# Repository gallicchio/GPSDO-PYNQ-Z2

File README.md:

# GPSDO-PYNQ-Z2

**Compare up to 13 GPS Disciplined Oscillators: 10 MHz and 1PPS**

A board for a [PYNQ-Z2](http://www.pynq.io/boards.html) that measures the phase of thirteen 10 MHz references
against each other in 12 ps steps, with a floor below a picosecond. Rev A is built and measured. **Rev B is in
hand, and has not been tested yet.**

Rev A after its bench life: the red wire and the blue resistors are the repairs.

<table>
<tr>
<td width="50%"></td>
<td width="50%"></td>
</tr>
<tr><td colspan="2">Rev A on its PYNQ-Z2, being measured against generators and a scope, October 2026.</td></tr>
</table>

Rev B, as drawn in KiCad:

<p>  </p>

Click any image to open it at full size.

## At a glance

| | |
|---|---|
| Inputs | 13 x 10 MHz and 12 x 1 pps, on SMA |
| Method | digital dual-mixer time difference (DDMTD), one helper clock for every channel |
| Step | 12.34 ps a count |
| Floor, rev A | Allan deviation 2.8e-12 at 1 s, 2.8e-15 at 1000 s; time deviation 0.18 ps at 1 s |
| 1 pps | a 10 ns counter across all twelve |
| Host | PYNQ-Z2 (Zynq-7020), on its Raspberry Pi header; a Python driver |
| Board | 207 x 180 mm, 4 layers, 27 SMA jacks, 5 V from the PYNQ |
| Cost | about $246 for two assembled (rev B's estimate, bare boards extra) |
| Status | rev A: built, repaired by hand, measured. Rev B: in hand, untested |

The files in this repository are rev B. Rev A is the tag `GPSDO-PYNQ-Z2-revA` and
[`GPSDO-PYNQ-Z2-revA.zip`](GPSDO-PYNQ-Z2-revA.zip).

## How it works

- **A helper clock 1234.4 Hz away from 10 MHz** samples every input in a flip-flop.
- **Each input comes out as a 1234.4 Hz beat** with the same phase, stretched 8101 times in time.
- **A plain counter in the FPGA** times the beat edges. No carry chains, no calibration: one count is 12.34 ps.
- **The helper is common to every channel**, so its own noise cancels when two channels are compared.
- **Only slow beats cross to the FPGA.** The 10 MHz never leaves the board.

## What rev A measured

One oven oscillator split to several inputs, so the inputs agree and what is left is the board.

| | measured |
|---|---|
| One beat edge, two inputs from one source | 5.4 ps rms: the counter's own step |
| Allan deviation | 2.8e-12 at 1 s, 2.8e-13 at 10 s, 2.8e-15 at 1000 s (50 Hz bandwidth) |
| Time deviation | 0.18 ps at 1 s, 0.06 ps at 10 s, 0.19 ps at 1000 s |
| Against two GPSDOs' own difference | the floor is 25 times below it at 1 s, 800 times at 10 s |

- These are for channels on the same helper buffer. Rev A has five buffers, and across them it is 12 times
  worse at 1 s. Rev B has one tree.
- **No GPSDO has been through this board yet.** The GPSDO curves were taken on another instrument.
- How it was measured: [`analysis/floor_compare/`](analysis/floor_compare/README.md).

## What rev A got wrong

| fault | on rev A | in rev B |
|---|---|---|
| The synthesizer slipped cycles while reporting lock | cured by a lower output drive, in software | a synthesizer with a proper clock input |
| Inputs with nothing plugged in oscillate | resistors added by hand | a parking jumper on every input |
| The analog 3.3 V had no plane | a strap wire | a plane |
| The 10 MHz monitor output leaks into the channels | kept at low drive | isolated |
| Five helper buffers: channels differ by group | measure within a group | one fan-out tree |

All of it, with the measurements: [`REVB_CHANGES.md`](REVB_CHANGES.md).

## Made with an AI

This was Jason's first board designed with an AI.

- **Nothing is drawn by hand.** About 18,000 lines of Python and Verilog generate the nineteen schematic
  sheets, place every part, route every track, and write the release, the handbook and the gateware.
- **The whole conversation is kept**: 46 rounds of prompts and answers, mistakes included, in
  [`docs/DESIGN_LOG.md`](docs/DESIGN_LOG.md).
- **Three other models reviewed it** before the order: [`design_review/`](design_review/README.md).

What it took to get a working board:

| what went wrong | how it was found |
|---|---|
| A release with no ground planes and no mounting holes passed every check | looking at a render |
| "0 violations" hid 598 errors | making the design-rule check ask more |
| Part rotations for assembly were wrong for six rounds | JLCPCB's own placement preview, the only authority |
| The synthesizer slipped while "locked" | the first real signals on the bench |

| | dates | days |
|---|---|---|
| Rev A design, to the order at JLCPCB | 2026-09-08 to 2026-09-15 | 8 |
| Rev A bring-up and measurement | 2026-09-30 to 2026-10-10 | 11 |
| Rev B design | 2026-10-09 to 2026-10-10 | 2 |
| Rev B ordered | 2026-10-22 | |

Jason Gallicchio, with Claude (Anthropic's Opus 5, Fable 5.1 and Opus 5.5, in Claude Code).

## What is here

| path | what |
|---|---|
| `*.kicad_sch`, `GPSDO-PYNQ-Z2.kicad_pcb` | the KiCad project, rev B |
| [`HANDBOOK.md`](HANDBOOK.md) | every connector, jumper and test point, and how to bring a board up |
| [`mfg/release/`](mfg/release/) | what was uploaded to JLCPCB: Gerbers, BOM, placement |
| [`gateware/`](gateware/README.md) | the Verilog, the Vivado build, the Python driver, the bench programs |
| `gen/`, `pcb/`, `mfg/` | the scripts that generate the design (`python3 build.py`) |
| [`analysis/`](analysis/floor_compare/README.md) | the floor, and how it compares |
| [`docs/DESIGN_LOG.md`](docs/DESIGN_LOG.md) | the design log: every prompt and answer |
| [`photos/`](photos/README.md) | rev A on the bench |

The board grew up in a private repository of the research group. Its commits are here; vendor datasheets are
not. Commit hashes quoted in the documents are the old ones: [`docs/COMMIT_MAP.tsv`](docs/COMMIT_MAP.tsv).

## Licence

Hardware under CERN-OHL-P-2.0, software under MIT: [`LICENSE`](LICENSE).

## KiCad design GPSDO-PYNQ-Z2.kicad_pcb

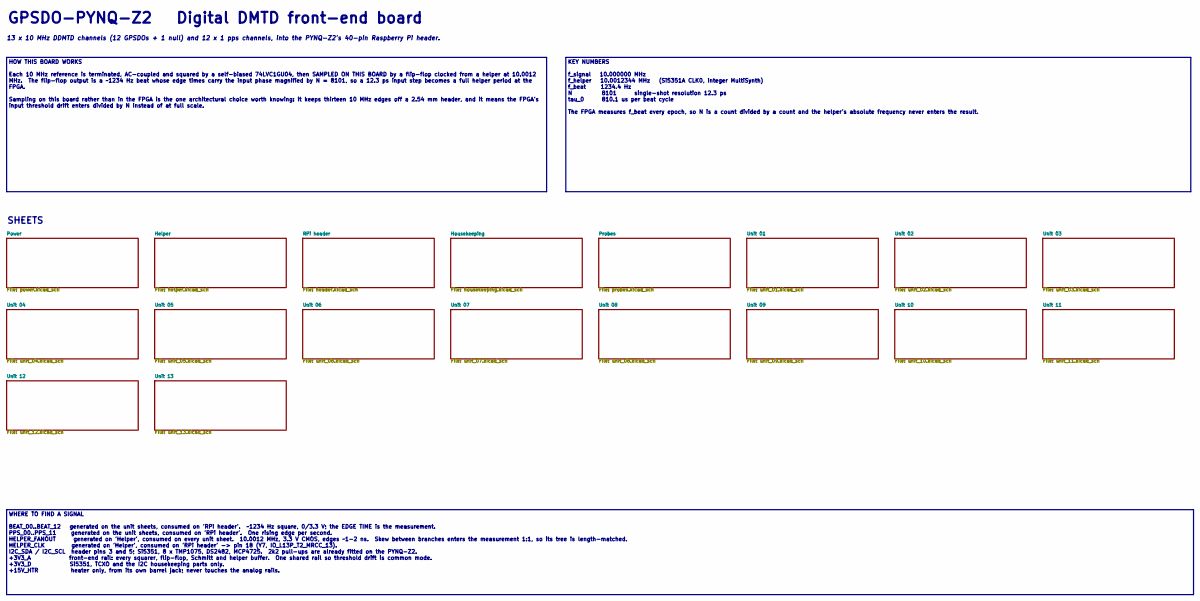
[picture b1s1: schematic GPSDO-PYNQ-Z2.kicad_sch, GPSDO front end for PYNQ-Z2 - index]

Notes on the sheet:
13 x 10 MHz DDMTD channels (12 GPSDOs + 1 null) and 12 x 1 pps channels, into the PYNQ-Z2's 40-pin Raspberry Pi header.
GPSDO-PYNQ-Z2 Digital DMTD front-end board
SHEETS
HOW THIS BOARD WORKS Each 10 MHz reference is terminated, AC-coupled and squared by a self-biased 74LVC1GU04, then SAMPLED ON THIS BOARD by a flip-flop clocked from a helper at 10.0012 MHz. The flip-flop output is a ~1234 Hz beat whose edge times carry the input phase magnified by N = 8101, so a 12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
KEY NUMBERS f_signal 10.000000 MHz f_helper 10.0012344 MHz (Si5351A CLK0, integer MultiSynth) f_beat 1234.4 Hz N 8101 single-shot resolution 12.3 ps tau_0 810.1 us per beat cycle The FPGA measures f_beat every epoch, so N is a count divided by a count and the helper's absolute frequency never enter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
WHERE TO FIND A SIGNAL BEAT_00..BEAT_12 generated on the unit sheets, consumed on 'RPi header'. ~1234 Hz square, 0/3.3 V; the EDGE TIME is the measurement. PPS_00..PPS_11 generated on the unit sheets, consumed on 'RPi header'. One rising edge per second. HELPER_FANOUT generated on 'Helper', consume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

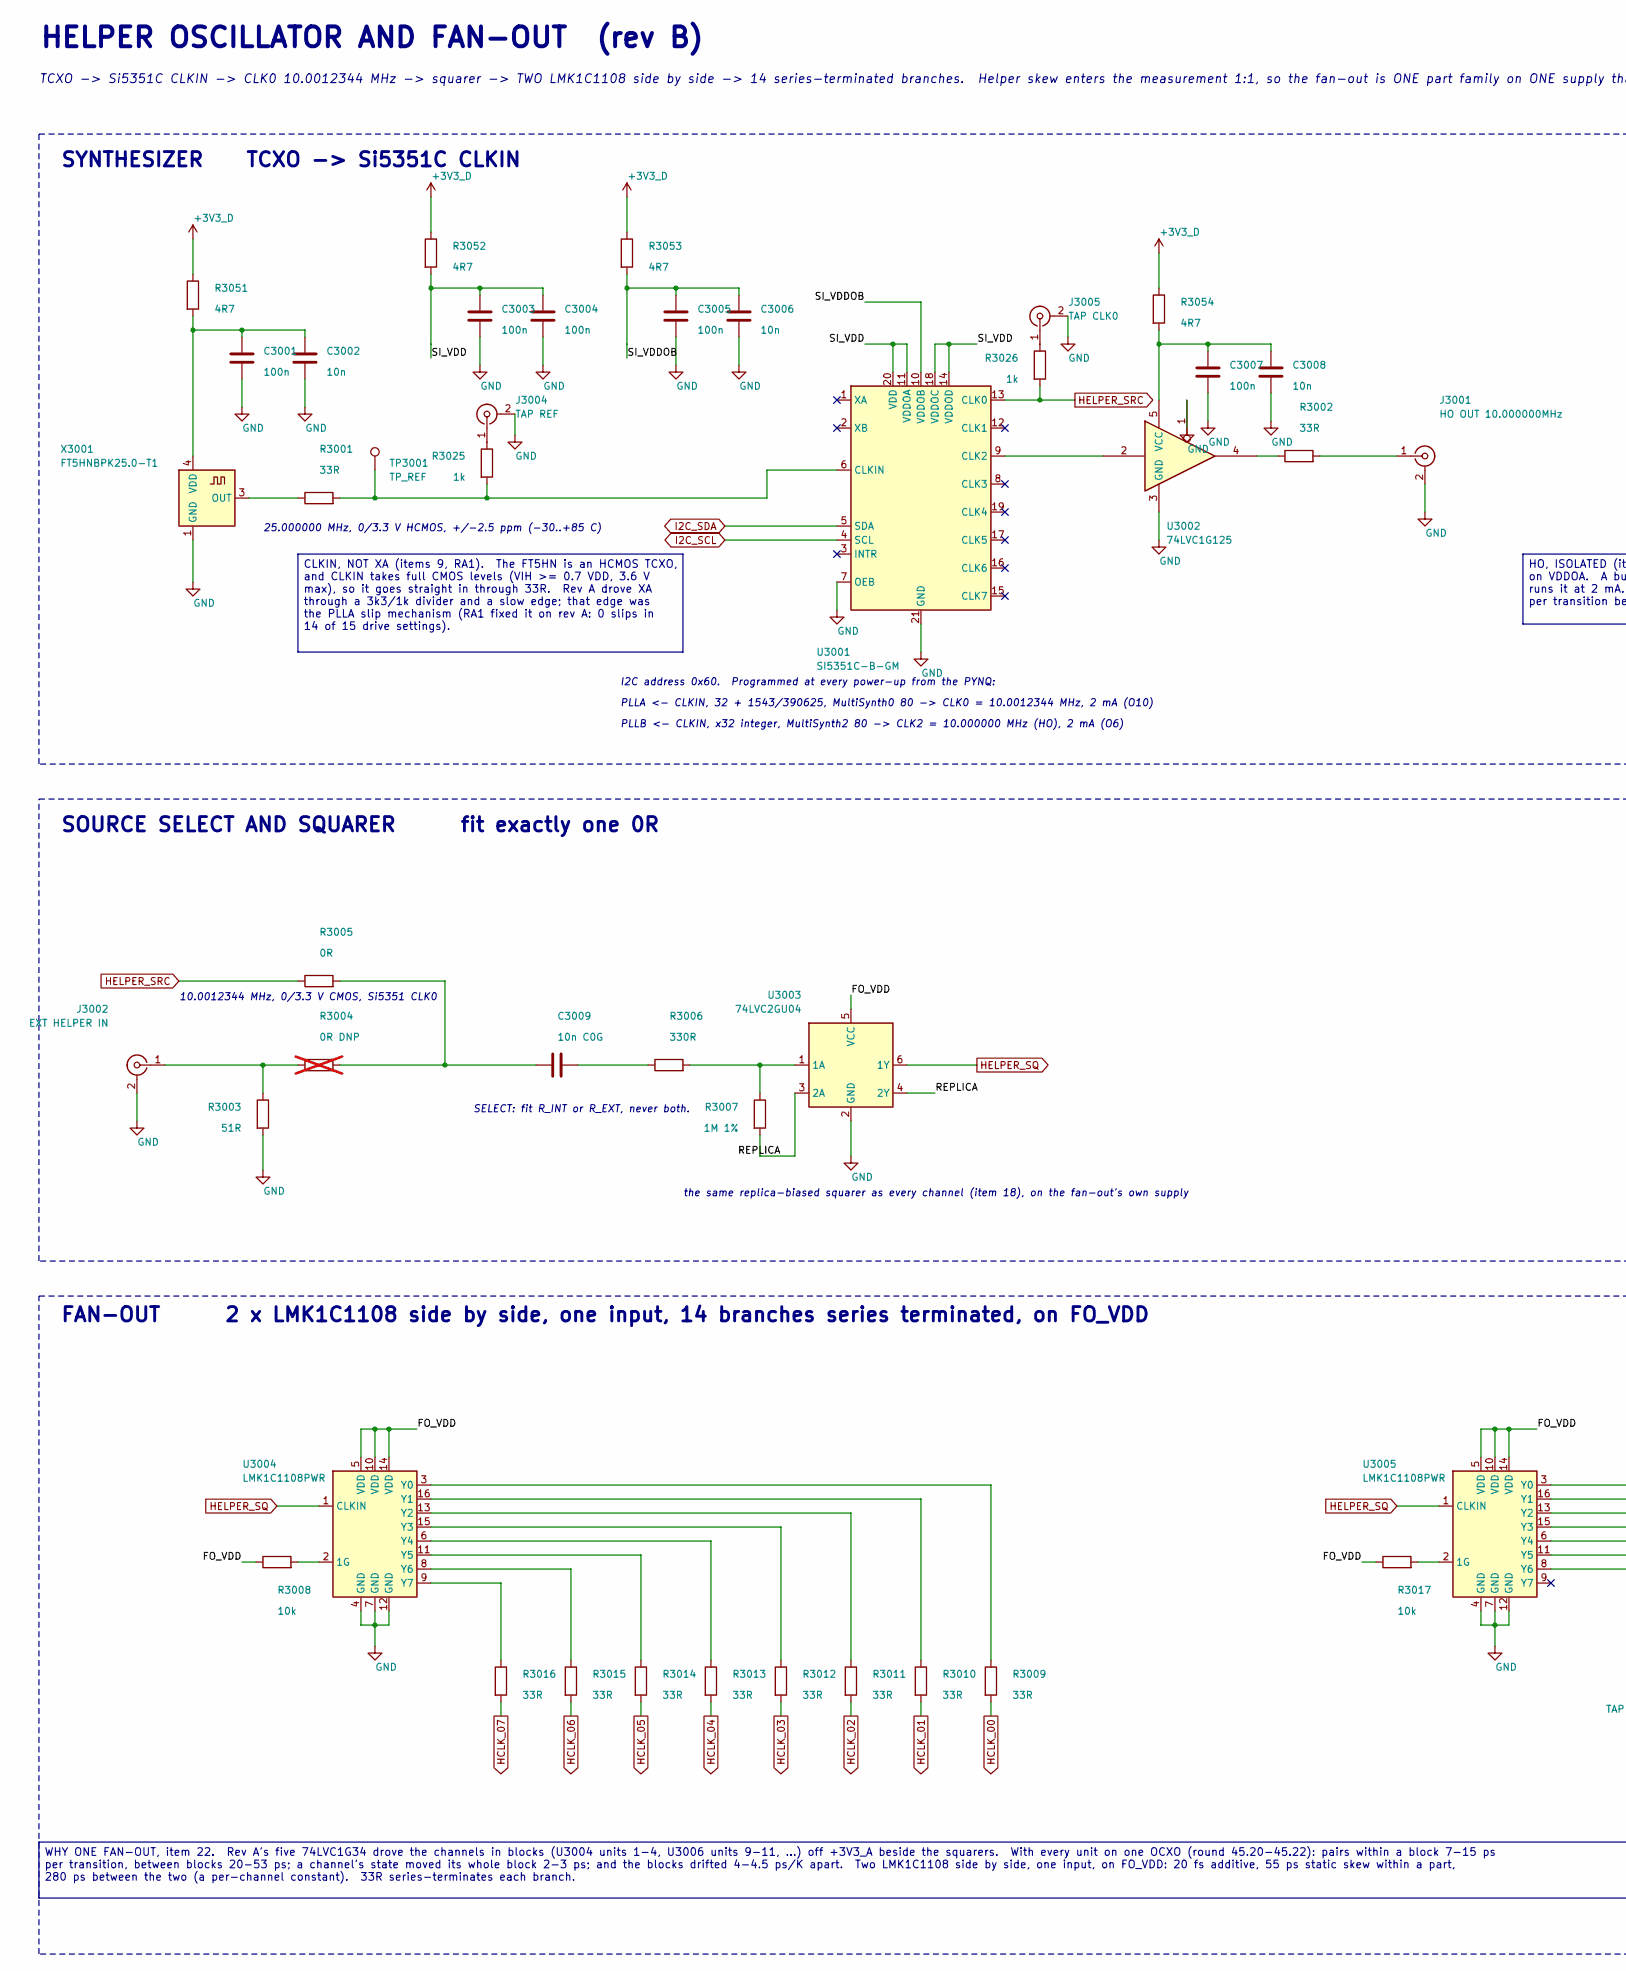
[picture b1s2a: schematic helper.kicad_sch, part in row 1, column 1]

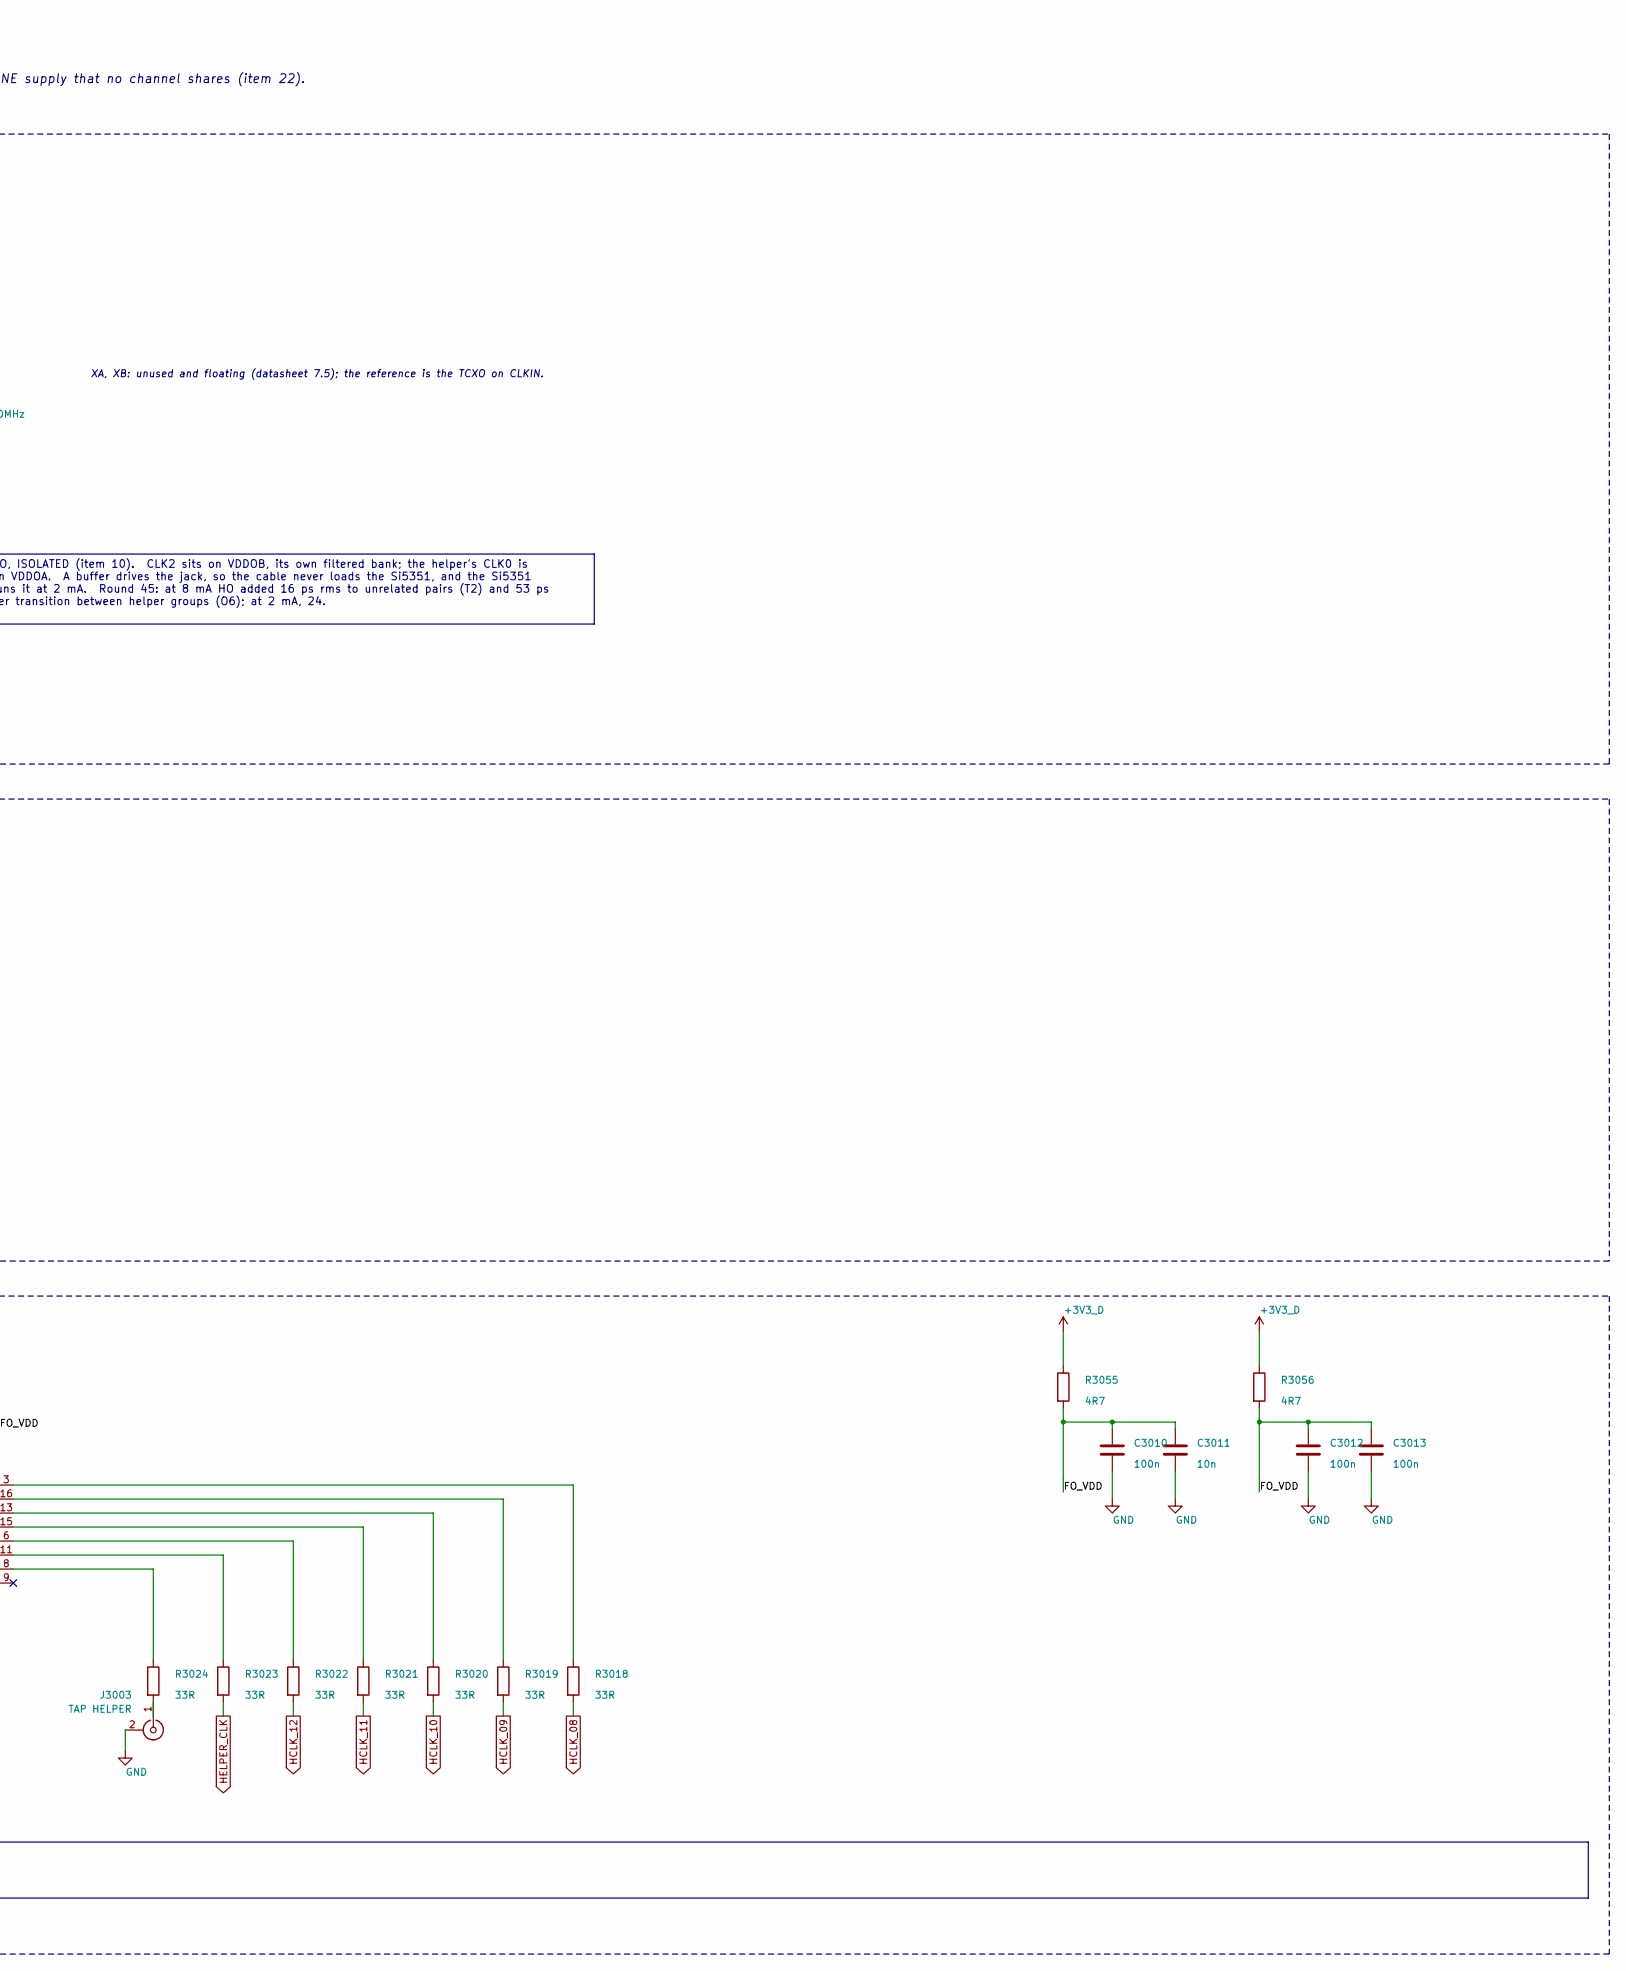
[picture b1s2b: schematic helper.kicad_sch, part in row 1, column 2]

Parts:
C3001, C3003, C3004, C3005, C3007, C3010, C3012, C3013: 100n; C_0805_2012Metric
C3002, C3006, C3008, C3011: 10n; C_0805_2012Metric
C3009: 10n C0G; C_0805_2012Metric
J3001: HO OUT 10.000000MHz; SMA_Vertical_THT_Universal; LCSC C496549
J3002: EXT HELPER IN; SMA_Vertical_THT_Universal; LCSC C496549
J3003: TAP HELPER; U.FL_Hirose_U.FL-R-SMT-1_Vertical; LCSC C88374
J3004: TAP REF; U.FL_Hirose_U.FL-R-SMT-1_Vertical; LCSC C88374
J3005: TAP CLK0; U.FL_Hirose_U.FL-R-SMT-1_Vertical; LCSC C88374
R3001, R3002, R3009, R3010, R3011, R3012, R3013, R3014, R3015, R3016, R3018, R3019, R3020, R3021, R3022, R3023, R3024: 33R; R_0805_2012Metric
R3003: 51R; R_0805_2012Metric
R3004: 0R DNP; R_0805_2012Metric; not fitted
R3005: 0R; R_0805_2012Metric
R3006: 330R; R_0805_2012Metric
R3007: 1M 1%; R_0805_2012Metric
R3008, R3017: 10k; R_0805_2012Metric
R3025, R3026: 1k; R_0805_2012Metric
R3051, R3052, R3053, R3054, R3055, R3056: 4R7; R_0805_2012Metric
TP3001: TP_REF; TestPoint_Pad_D1.5mm
U3001: SI5351C-B-GM; QFN-20-1EP_4x4mm_P0.5mm_EP2.7x2.7mm; LCSC C3608122
U3002: 74LVC1G125; SOT-23-5; LCSC C23654
U3003: 74LVC2GU04; SOT-363_SC-70-6; LCSC C116660
U3004, U3005: LMK1C1108PWR; TSSOP-16_4.4x5mm_P0.65mm; LCSC C2868241
X3001: FT5HNBPK25.0-T1; Oscillator_SMD_Fox_FT5H_5.0x3.2mm; LCSC C5742665

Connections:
+3V3_D: R3051.1, R3052.1, R3053.1, R3054.1, R3055.1, R3056.1; also elsewhere on the board
/Helper/FO_VDD: C3010.1, C3011.1, C3012.1, C3013.1, R3008.1, R3017.1, R3055.2, R3056.2, U3003.5 (VCC), U3004.5 (VDD), U3004.10 (VDD), U3004.14 (VDD), U3005.5 (VDD), U3005.10 (VDD), U3005.14 (VDD)
/Helper/REPLICA: R3007.2, U3003.3 (2A), U3003.4 (2Y)
/Helper/SI_VDD: C3003.1, C3004.1, R3052.2, U3001.11 (VDDOA), U3001.14 (VDDOD), U3001.18 (VDDOC), U3001.20 (VDD)
/Helper/SI_VDDOB: C3005.1, C3006.1, R3053.2, U3001.10 (VDDOB)
GND: C3001.2, C3002.2, C3003.2, C3004.2, C3005.2, C3006.2, C3007.2, C3008.2, C3010.2, C3011.2, C3012.2, C3013.2, J3001.2 (Ext), J3002.2 (Ext), J3003.2 (Ext), J3004.2 (Ext), J3005.2 (Ext), R3003.2, U3001.7 (OEB), U3001.21 (GND), U3002.1, U3002.3 (GND), U3003.2 (GND), U3004.4 (GND), U3004.7 (GND), U3004.12 (GND), U3005.4 (GND), U3005.7 (GND), U3005.12 (GND), X3001.1 (GND), X3001.2 (GND); also elsewhere on the board
HCLK_00: R3009.2; also elsewhere on the board
HCLK_01: R3010.2; also elsewhere on the board
HCLK_02: R3011.2; also elsewhere on the board
HCLK_03: R3012.2; also elsewhere on the board
HCLK_04: R3013.2; also elsewhere on the board
HCLK_05: R3014.2; also elsewhere on the board
HCLK_06: R3015.2; also elsewhere on the board
HCLK_07: R3016.2; also elsewhere on the board
HCLK_08: R3018.2; also elsewhere on the board
HCLK_09: R3019.2; also elsewhere on the board
HCLK_10: R3020.2; also elsewhere on the board
HCLK_11: R3021.2; also elsewhere on the board
HCLK_12: R3022.2; also elsewhere on the board
HELPER_CLK: R3023.2; also elsewhere on the board
HELPER_SQ: U3003.6 (1Y), U3004.1 (CLKIN), U3005.1 (CLKIN)
HELPER_SRC: R3005.1, R3026.2, U3001.13 (CLK0)
I2C_SCL: U3001.4 (SCL); also elsewhere on the board
I2C_SDA: U3001.5 (SDA); also elsewhere on the board
unnamed: C3009.1, R3004.2, R3005.2
unnamed: C3009.2, R3006.1
unnamed: J3001.1 (In), R3002.2
unnamed: J3002.1 (In), R3003.1, R3004.1
unnamed: J3003.1 (In), R3024.2
unnamed: J3004.1 (In), R3025.1
unnamed: J3005.1 (In), R3026.1
unnamed: R3002.1, U3002.4
unnamed: U3001.9 (CLK2), U3002.2
unnamed: R3001.2, R3025.2, TP3001.1, U3001.6 (CLKIN)
unnamed: C3007.1, C3008.1, R3054.2, U3002.5 (VCC)
unnamed: R3006.2, R3007.1, U3003.1 (1A)
unnamed: R3008.2, U3004.2 (1G)
unnamed: R3009.1, U3004.3 (Y0)
unnamed: R3010.1, U3004.16 (Y1)
unnamed: R3011.1, U3004.13 (Y2)
unnamed: R3012.1, U3004.15 (Y3)
unnamed: R3013.1, U3004.6 (Y4)
unnamed: R3014.1, U3004.11 (Y5)
unnamed: R3015.1, U3004.8 (Y6)
unnamed: R3016.1, U3004.9 (Y7)
unnamed: R3017.2, U3005.2 (1G)
unnamed: R3018.1, U3005.3 (Y0)
unnamed: R3019.1, U3005.16 (Y1)
unnamed: R3020.1, U3005.13 (Y2)
unnamed: R3021.1, U3005.15 (Y3)
unnamed: R3022.1, U3005.6 (Y4)
unnamed: R3023.1, U3005.11 (Y5)
unnamed: R3024.1, U3005.8 (Y6)
unnamed: R3001.1, X3001.3 (OUT)
unnamed: C3001.1, C3002.1, R3051.2, X3001.4 (VDD)

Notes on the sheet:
SYNTHESIZER TCXO -> Si5351C CLKIN
PLLA <- CLKIN, 32 + 1543/390625, MultiSynth0 80 -> CLK0 = 10.0012344 MHz, 2 mA (O10)
PLLB <- CLKIN, x32 integer, MultiSynth2 80 -> CLK2 = 10.000000 MHz (HO), 2 mA (O6)
SELECT: fit R_INT or R_EXT, never both.
I2C address 0x60. Programmed at every power-up from the PYNQ:
HELPER OSCILLATOR AND FAN-OUT (rev B)
TCXO -> Si5351C CLKIN -> CLK0 10.0012344 MHz -> squarer -> TWO LMK1C1108 side by side -> 14 series-terminated branches. Helper skew enters the measurement 1:1, so the fan-out is ONE part family on ONE supply that no channel shares (item 22).
10.0012344 MHz, 0/3.3 V CMOS, Si5351 CLK0
the same replica-biased squarer as every channel (item 18), on the fan-out's own supply
FAN-OUT 2 x LMK1C1108 side by side, one input, 14 branches series terminated, on FO_VDD
SOURCE SELECT AND SQUARER fit exactly one 0R
XA, XB: unused and floating (datasheet 7.5); the reference is the TCXO on CLKIN.
25.000000 MHz, 0/3.3 V HCMOS, +/-2.5 ppm (-30..+85 C)
WHY ONE FAN-OUT, item 22. Rev A's five 74LVC1G34 drove the channels in blocks (U3004 units 1-4, U3006 units 9-11, ...) off +3V3_A beside the squarers. With every unit on one OCXO (round 45.20-45.22): pairs within a block 7-15 ps per transition, between blocks 20-53 ps; a channel's state moved its w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
HO, ISOLATED (item 10). CLK2 sits on VDDOB, its own filtered bank; the helper's CLK0 is on VDDOA. A buffer drives the jack, so the cable never loads the Si5351, and the Si5351 runs it at 2 mA. Round 45: at 8 mA HO added 16 ps rms to unrelated pairs (T2) and 53 ps per transition between helper group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
CLKIN, NOT XA (items 9, RA1). The FT5HN is an HCMOS TCXO, and CLKIN takes full CMOS levels (VIH >= 0.7 VDD, 3.6 V max), so it goes straight in through 33R. Rev A drove XA through a 3k3/1k divider and a slow edge; that edge was the PLLA slip mechanism (RA1 fixed it on rev A: 0 slips in 14 of 15 driv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

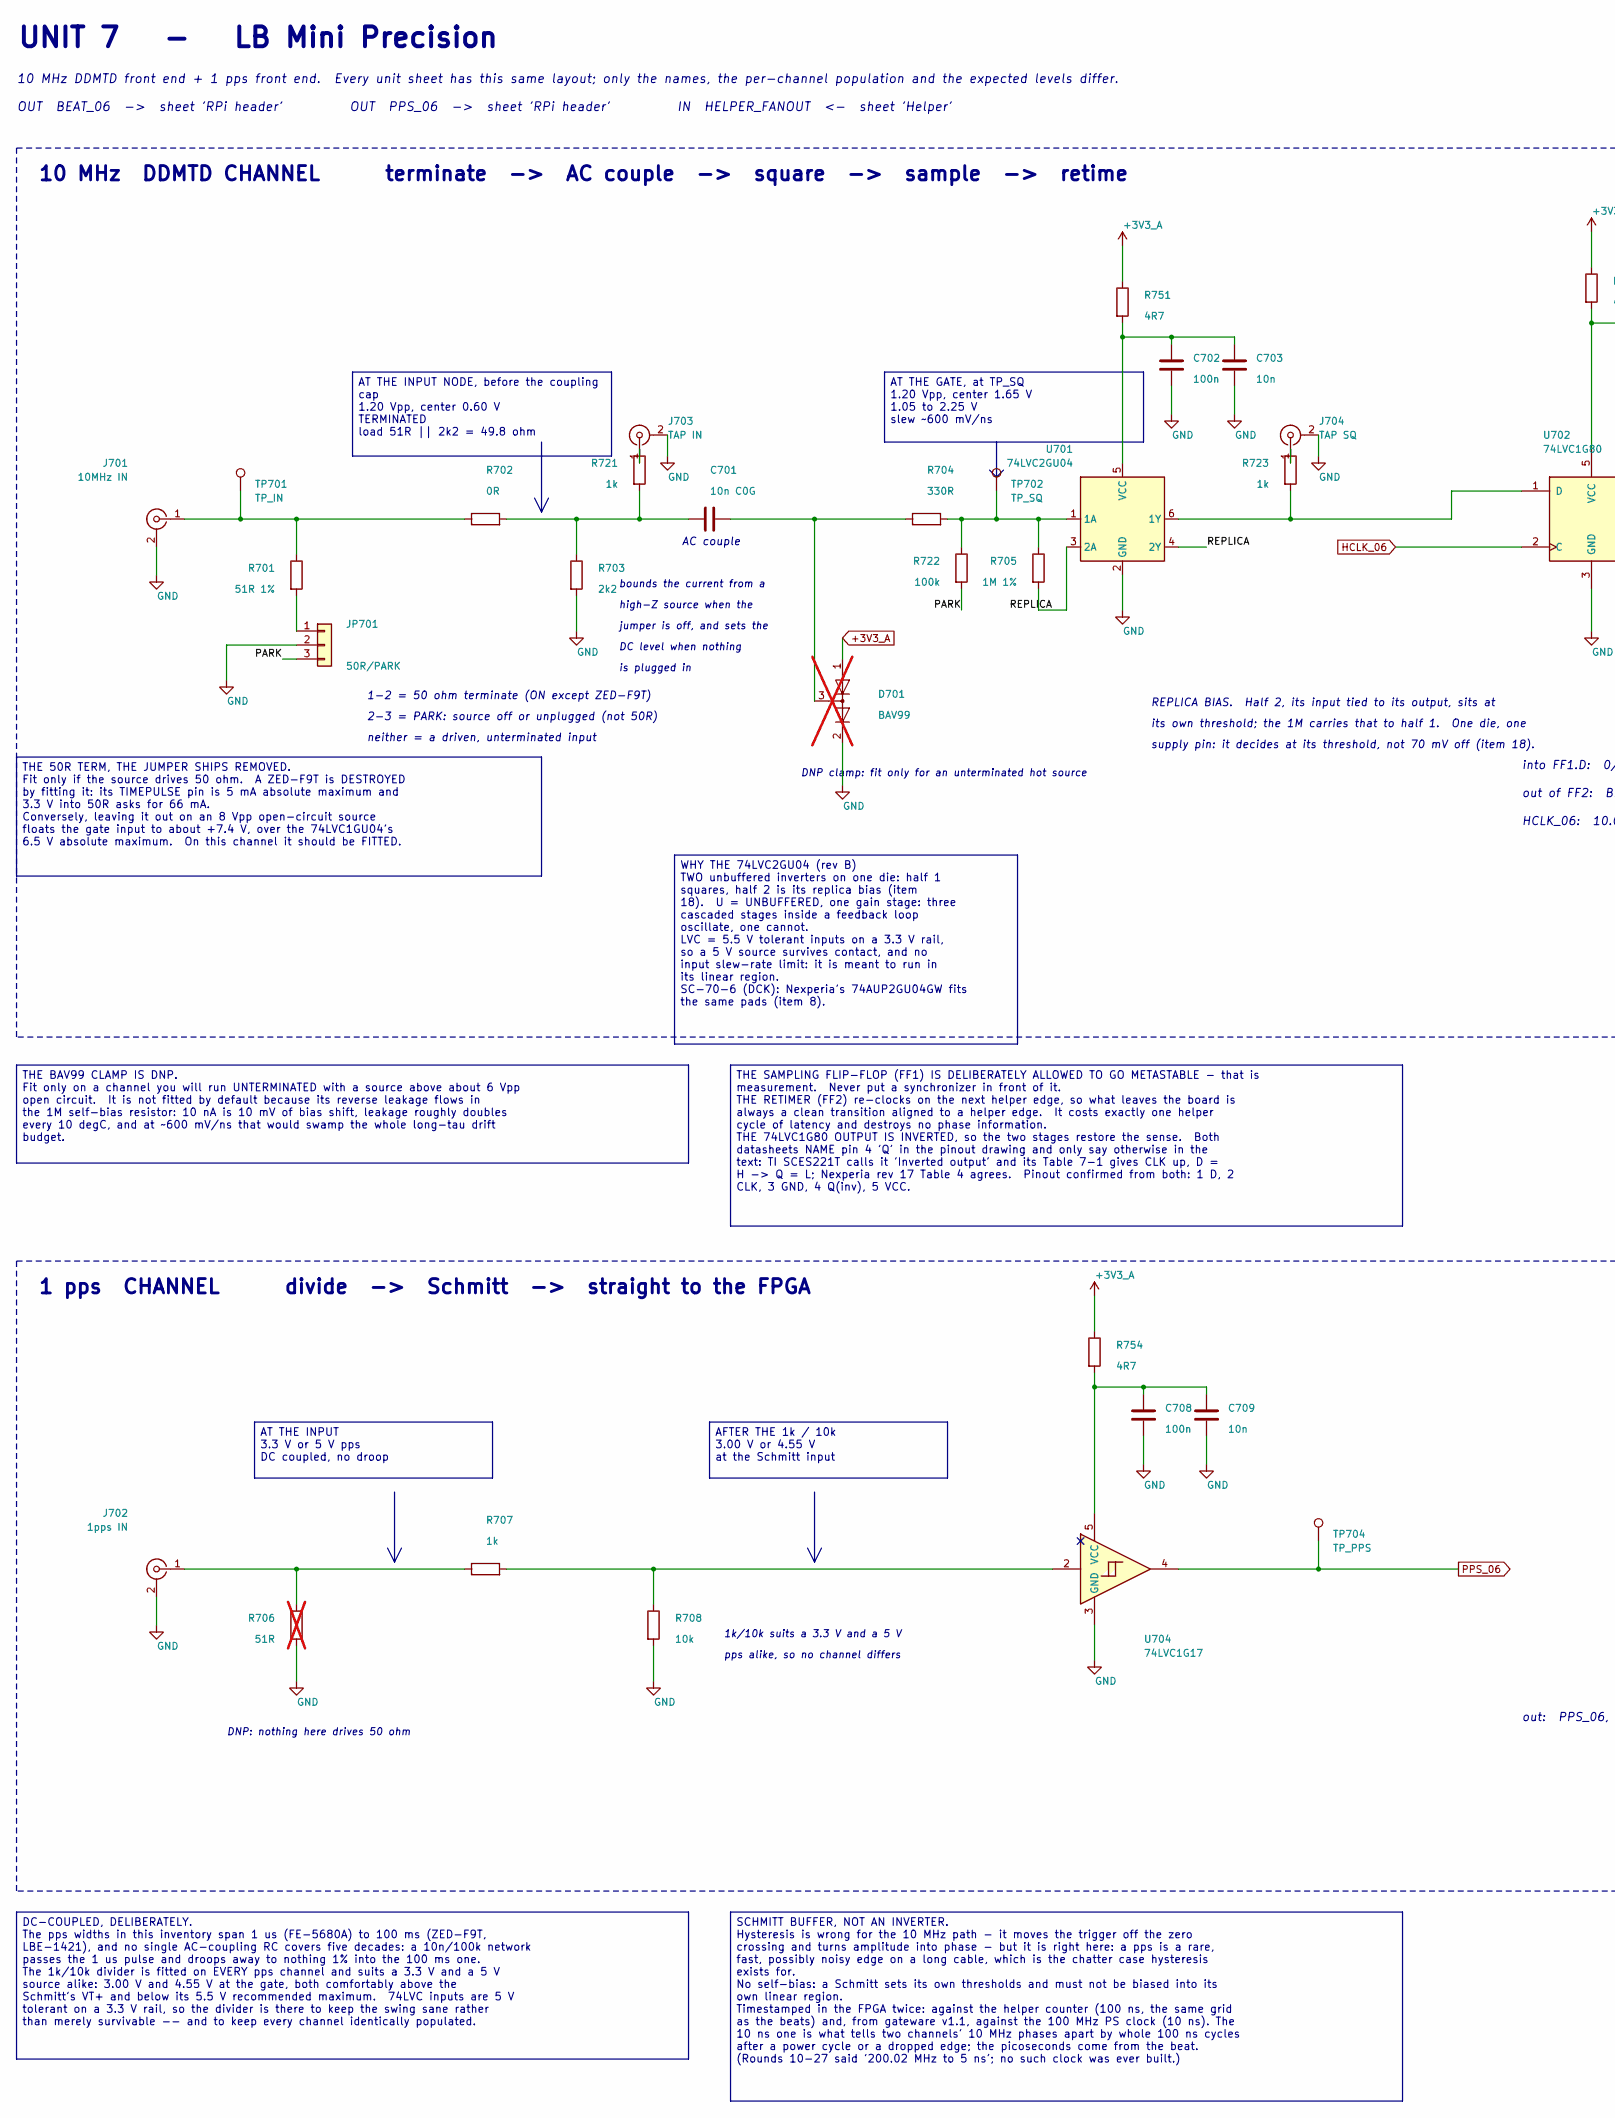
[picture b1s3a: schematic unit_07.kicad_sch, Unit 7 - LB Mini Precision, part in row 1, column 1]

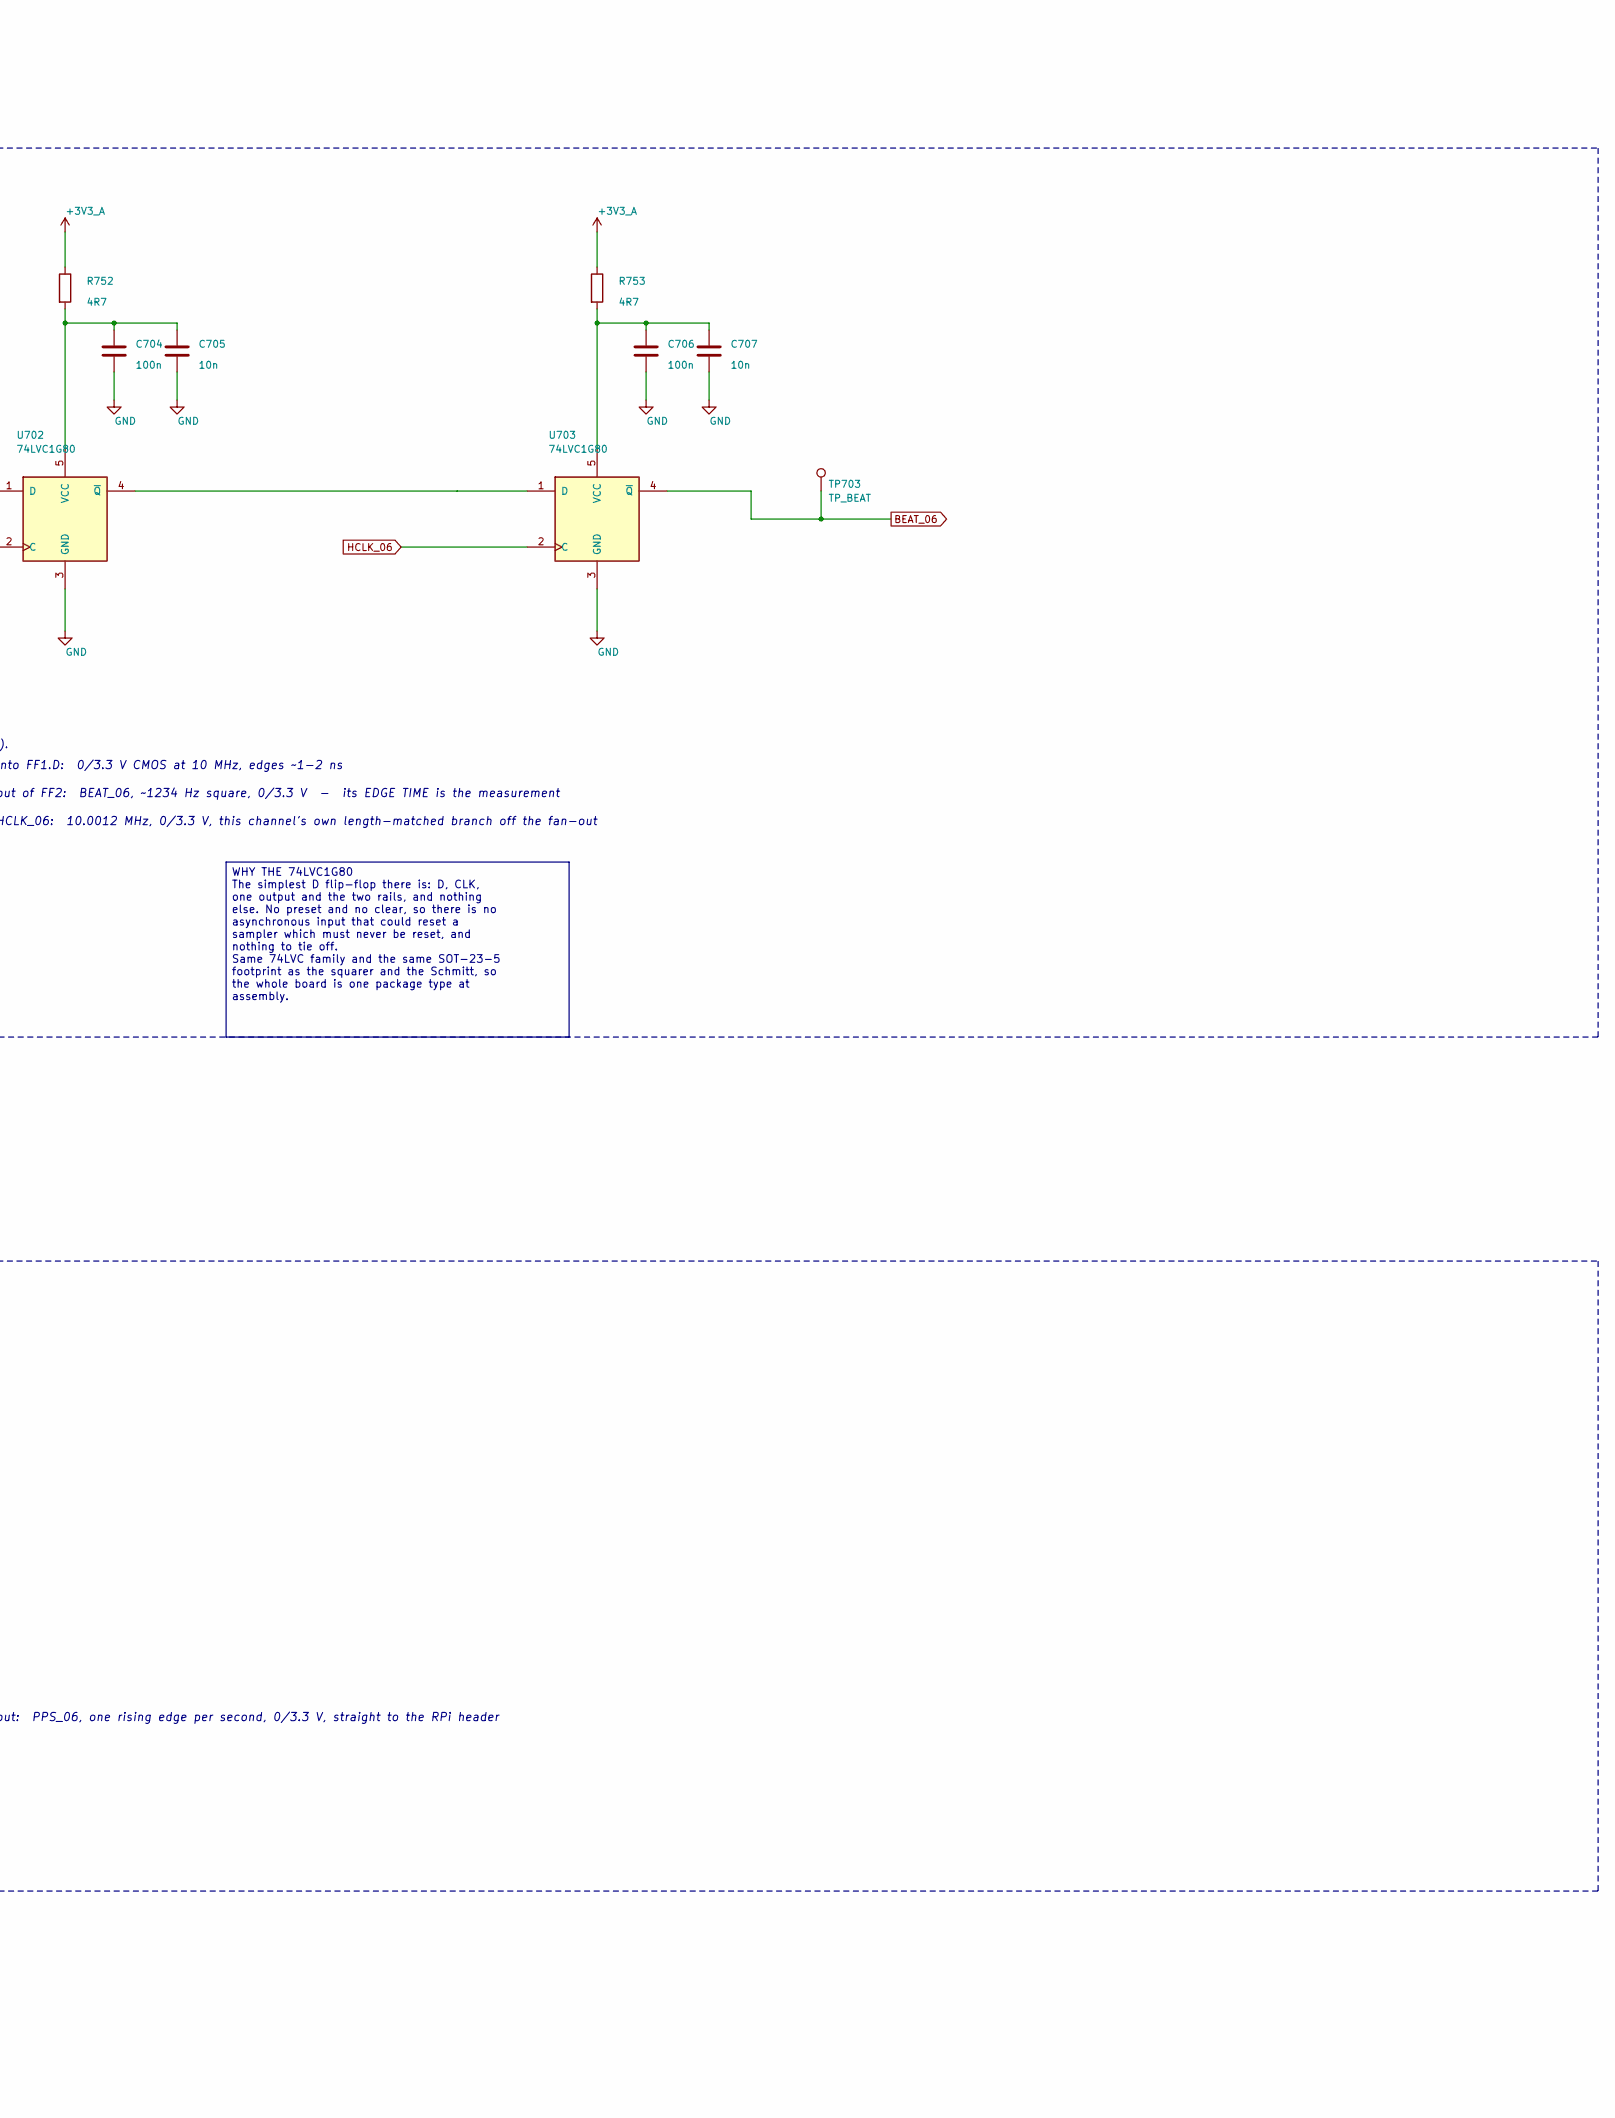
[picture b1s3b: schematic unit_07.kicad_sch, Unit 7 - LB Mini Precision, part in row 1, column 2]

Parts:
C701: 10n C0G; C_0805_2012Metric
C702, C704, C706, C708: 100n; C_0805_2012Metric
C703, C705, C707, C709: 10n; C_0805_2012Metric
D701: BAV99; SOT-23; LCSC C916421; not fitted
J701: 10MHz IN; SMA_Vertical_THT_Universal; LCSC C496549
J702: 1pps IN; SMA_Vertical_THT_Universal; LCSC C496549
J703: TAP IN; U.FL_Hirose_U.FL-R-SMT-1_Vertical; LCSC C88374
J704: TAP SQ; U.FL_Hirose_U.FL-R-SMT-1_Vertical; LCSC C88374
JP701: 50R/PARK; PinHeader_1x03_P2.54mm_Vertical
R701: 51R 1%; R_0805_2012Metric
R702: 0R; R_0805_2012Metric
R703: 2k2; R_0805_2012Metric
R704: 330R; R_0805_2012Metric
R705: 1M 1%; R_0805_2012Metric
R706: 51R; R_0805_2012Metric; not fitted
R707, R721, R723: 1k; R_0805_2012Metric
R708: 10k; R_0805_2012Metric
R722: 100k; R_0805_2012Metric
R751, R752, R753, R754: 4R7; R_0805_2012Metric
TP701: TP_IN; TestPoint_Pad_D1.5mm
TP702: TP_SQ; TestPoint_Pad_D1.5mm
TP703: TP_BEAT; TestPoint_Pad_D1.5mm
TP704: TP_PPS; TestPoint_Pad_D1.5mm
U701: 74LVC2GU04; SOT-363_SC-70-6; LCSC C116660
U702, U703: 74LVC1G80; SOT-23-5; LCSC C42879
U704: 74LVC1G17; SOT-23-5; LCSC C7836

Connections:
+3V3_A: D701.1 (K), R751.1, R752.1, R753.1, R754.1; also elsewhere on the board
/Unit 07/PARK: JP701.3, R722.2
/Unit 07/REPLICA: R705.2, U701.3 (2A), U701.4 (2Y)
BEAT_06: TP703.1, U703.4 (~Q); also elsewhere on the board
GND: C702.2, C703.2, C704.2, C705.2, C706.2, C707.2, C708.2, C709.2, D701.2 (A), J701.2 (Ext), J702.2 (Ext), J703.2 (Ext), J704.2 (Ext), JP701.2, R703.2, R706.2, R708.2, U701.2 (GND), U702.3 (GND), U703.3 (GND), U704.3 (GND); also elsewhere on the board
HCLK_06: U702.2 (C), U703.2 (C); also elsewhere on the board
unnamed: C701.1, R702.2, R703.1, R721.2
unnamed: C701.2, D701.3 (K), R704.1
unnamed: J701.1 (In), R701.1, R702.1, TP701.1
unnamed: J702.1 (In), R706.1, R707.1
unnamed: J703.1 (In), R721.1
unnamed: J704.1 (In), R723.1
unnamed: JP701.1, R701.2
unnamed: R707.2, R708.1, U704.2
unnamed: R704.2, R705.1, R722.1, TP702.1, U701.1 (1A)
unnamed: R723.2, U701.6 (1Y), U702.1 (D)
unnamed: C702.1, C703.1, R751.2, U701.5 (VCC)
unnamed: C704.1, C705.1, R752.2, U702.5 (VCC)
unnamed: U702.4 (~Q), U703.1 (D)
unnamed: C706.1, C707.1, R753.2, U703.5 (VCC)
unnamed: C708.1, C709.1, R754.2, U704.5 (VCC)
PPS_06: TP704.1, U704.4; also elsewhere on the board

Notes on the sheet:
10 MHz DDMTD front end + 1 pps front end. Every unit sheet has this same layout; only the names, the per-channel population and the expected levels differ.
DNP: nothing here drives 50 ohm
jumper is off, and sets the
1k/10k suits a 3.3 V and a 5 V
out: PPS_06, one rising edge per second, 0/3.3 V, straight to the RPi header
10 MHz DDMTD CHANNEL terminate -> AC couple -> square -> sample -> retime
UNIT 7 - LB Mini Precision
supply pin: it decides at its threshold, not 70 mV off (item 18).
neither = a driven, unterminated input
OUT BEAT_06 -> sheet 'RPi header' OUT PPS_06 -> sheet 'RPi header' IN HELPER_FANOUT <- sheet 'Helper'
its own threshold; the 1M carries that to half 1. One die, one
1 pps CHANNEL divide -> Schmitt -> straight to the FPGA
high-Z source when the
2-3 = PARK: source off or unplugged (not 50R)
bounds the current from a
1-2 = 50 ohm terminate (ON except ZED-F9T)
pps alike, so no channel differs
out of FF2: BEAT_06, ~1234 Hz square, 0/3.3 V - its EDGE TIME is the measurement
into FF1.D: 0/3.3 V CMOS at 10 MHz, edges ~1-2 ns
AC couple
DC level when nothing
DNP clamp: fit only for an unterminated hot source
REPLICA BIAS. Half 2, its input tied to its output, sits at
is plugged in
HCLK_06: 10.0012 MHz, 0/3.3 V, this channel's own length-matched branch off the fan-out
AT THE GATE, at TP_SQ 1.20 Vpp, center 1.65 V 1.05 to 2.25 V slew ~600 mV/ns
THE BAV99 CLAMP IS DNP. Fit only on a channel you will run UNTERMINATED with a source above about 6 Vpp open circuit. It is not fitted by default because its reverse leakage flows in the 1M self-bias resistor: 10 nA is 10 mV of bias shift, leakage roughly doubles every 10 degC, and at ~600 mV/ns th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
WHY THE 74LVC1G80 The simplest D flip-flop there is: D, CLK, one output and the two rails, and nothing else. No preset and no clear, so there is no asynchronous input that could reset a sampler which must never be reset, and nothing to tie off. Same 74LVC family and the same SOT-23-5 footprint as t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
AFTER THE 1k / 10k 3.00 V or 4.55 V at the Schmitt input
WHY THE 74LVC2GU04 (rev B) TWO unbuffered inverters on one die: half 1 squares, half 2 is its replica bias (item 18). U = UNBUFFERED, one gain stage: three cascaded stages inside a feedback loop oscillate, one cannot. LVC = 5.5 V tolerant inputs on a 3.3 V rail, so a 5 V source survives contact, an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
AT THE INPUT NODE, before the coupling cap 1.20 Vpp, center 0.60 V TERMINATED load 51R || 2k2 = 49.8 ohm
THE SAMPLING FLIP-FLOP (FF1) IS DELIBERATELY ALLOWED TO GO METASTABLE - that is measurement. Never put a synchronizer in front of it. THE RETIMER (FF2) re-clocks on the next helper edge, so what leaves the board is always a clean transition aligned to a helper edge. It costs exactly one helper cycl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
THE 50R TERM, THE JUMPER SHIPS REMOVED. Fit only if the source drives 50 ohm. A ZED-F9T is DESTROYED by fitting it: its TIMEPULSE pin is 5 mA absolute maximum and 3.3 V into 50R asks for 66 mA. Conversely, leaving it out on an 8 Vpp open-circuit source floats the gate input to about +7.4 V, over th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
DC-COUPLED, DELIBERATELY. The pps widths in this inventory span 1 us (FE-5680A) to 100 ms (ZED-F9T, LBE-1421), and no single AC-coupling RC covers five decades: a 10n/100k network passes the 1 us pulse and droops away to nothing 1% into the 100 ms one. The 1k/10k divider is fitted on EVERY pps chan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
AT THE INPUT 3.3 V or 5 V pps DC coupled, no droop
SCHMITT BUFFER, NOT AN INVERTER. Hysteresis is wrong for the 10 MHz path - it moves the trigger off the zero crossing and turns amplitude into phase - but it is right here: a pps is a rare, fast, possibly noisy edge on a long cable, which is the chatter case hysteresis exists for. No self-bias: a S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
